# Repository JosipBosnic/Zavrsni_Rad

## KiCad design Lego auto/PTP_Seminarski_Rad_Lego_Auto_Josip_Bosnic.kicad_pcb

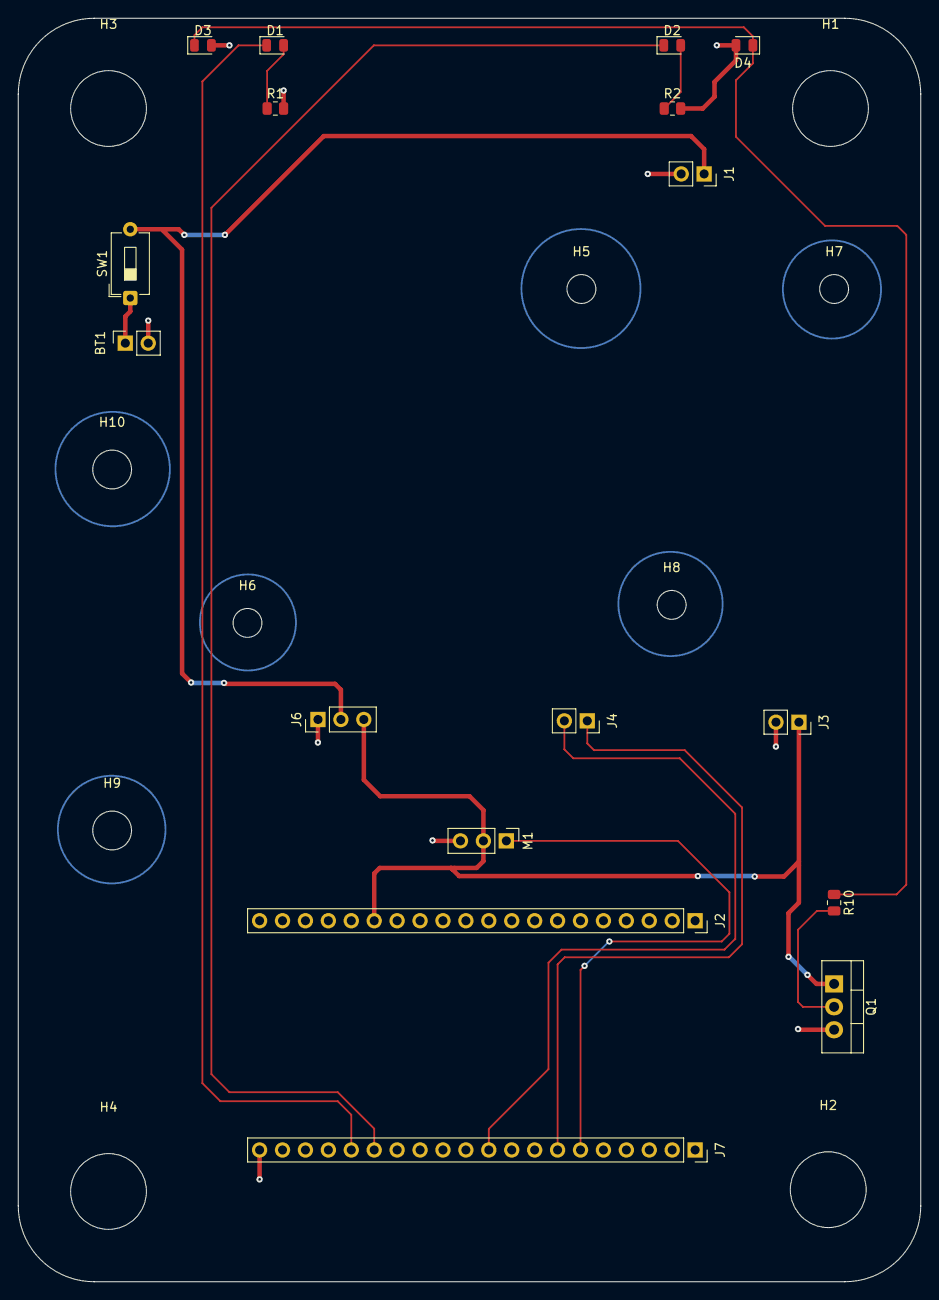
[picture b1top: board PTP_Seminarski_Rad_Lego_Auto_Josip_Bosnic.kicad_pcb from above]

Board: 2 copper layers, 100.0 x 140.0 mm, 27 parts (0 on the bottom side), 13 nets.

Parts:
BT1: Battery; PinSocket_1x02_P2.54mm_Vertical
D1, D2, D3, D4: LED; LED_0805_2012Metric
H1, H2, H3, H4: MountingHole; MountingHole_8.4mm_M8
H5: Hmost1; MountingHole_3.2mm_M3
H6: Hmost2; MountingHole_3.2mm_M3
H7: istosmjerni1; MountingHole_3.2mm_M3
H8: istosmjerni2; MountingHole_3.2mm_M3
H9: baterija1; MountingHole_4.3mm_M4
H10: baterija2; MountingHole_4.3mm_M4
J1, J3, J4: Conn_01x02; PinSocket_1x02_P2.54mm_Vertical
J2, J7: Conn_01x20_Socket; PinSocket_1x20_P2.54mm_Vertical
J6: Conn_01x03_Socket; PinHeader_1x03_P2.54mm_Vertical
M1: Motor_Servo; PinHeader_1x03_P2.54mm_Vertical
Q1: IRLZ44N; TO-220-3_Vertical
R1, R2, R10: 330 R; R_0805_2012Metric
SW1: SW_SPST; SW_DIP_SPSTx01_Slide_6.7x4.1mm_W7.62mm_P2.54mm_LowProfile

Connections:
+5V: J2.15, J3.1, J6.3, M1.2 (+), Q1.1 (G)
+BATT: J1.1, J6.2, SW1.2 (B)
-BATT: BT1.2 (-), D3.2 (A), D4.2 (A), J1.2, J3.2, J6.1, J7.20, M1.3 (-), Q1.3 (S), R1.2, R2.2
/IN1: J4.1, J7.7
/IN2: J4.2, J7.10
/servosignal: J7.6, M1.1 (PWM)
unnamed: BT1.1 (+), SW1.1 (A)
unnamed: D1.2 (A), R1.1
unnamed: D2.2 (A), R2.1
unnamed: Q1.2 (D), R10.2
Q1: D1.1 (K), J7.16
Q2: D2.1 (K), J7.15
Q3: D3.1 (K), D4.1 (K), R10.1

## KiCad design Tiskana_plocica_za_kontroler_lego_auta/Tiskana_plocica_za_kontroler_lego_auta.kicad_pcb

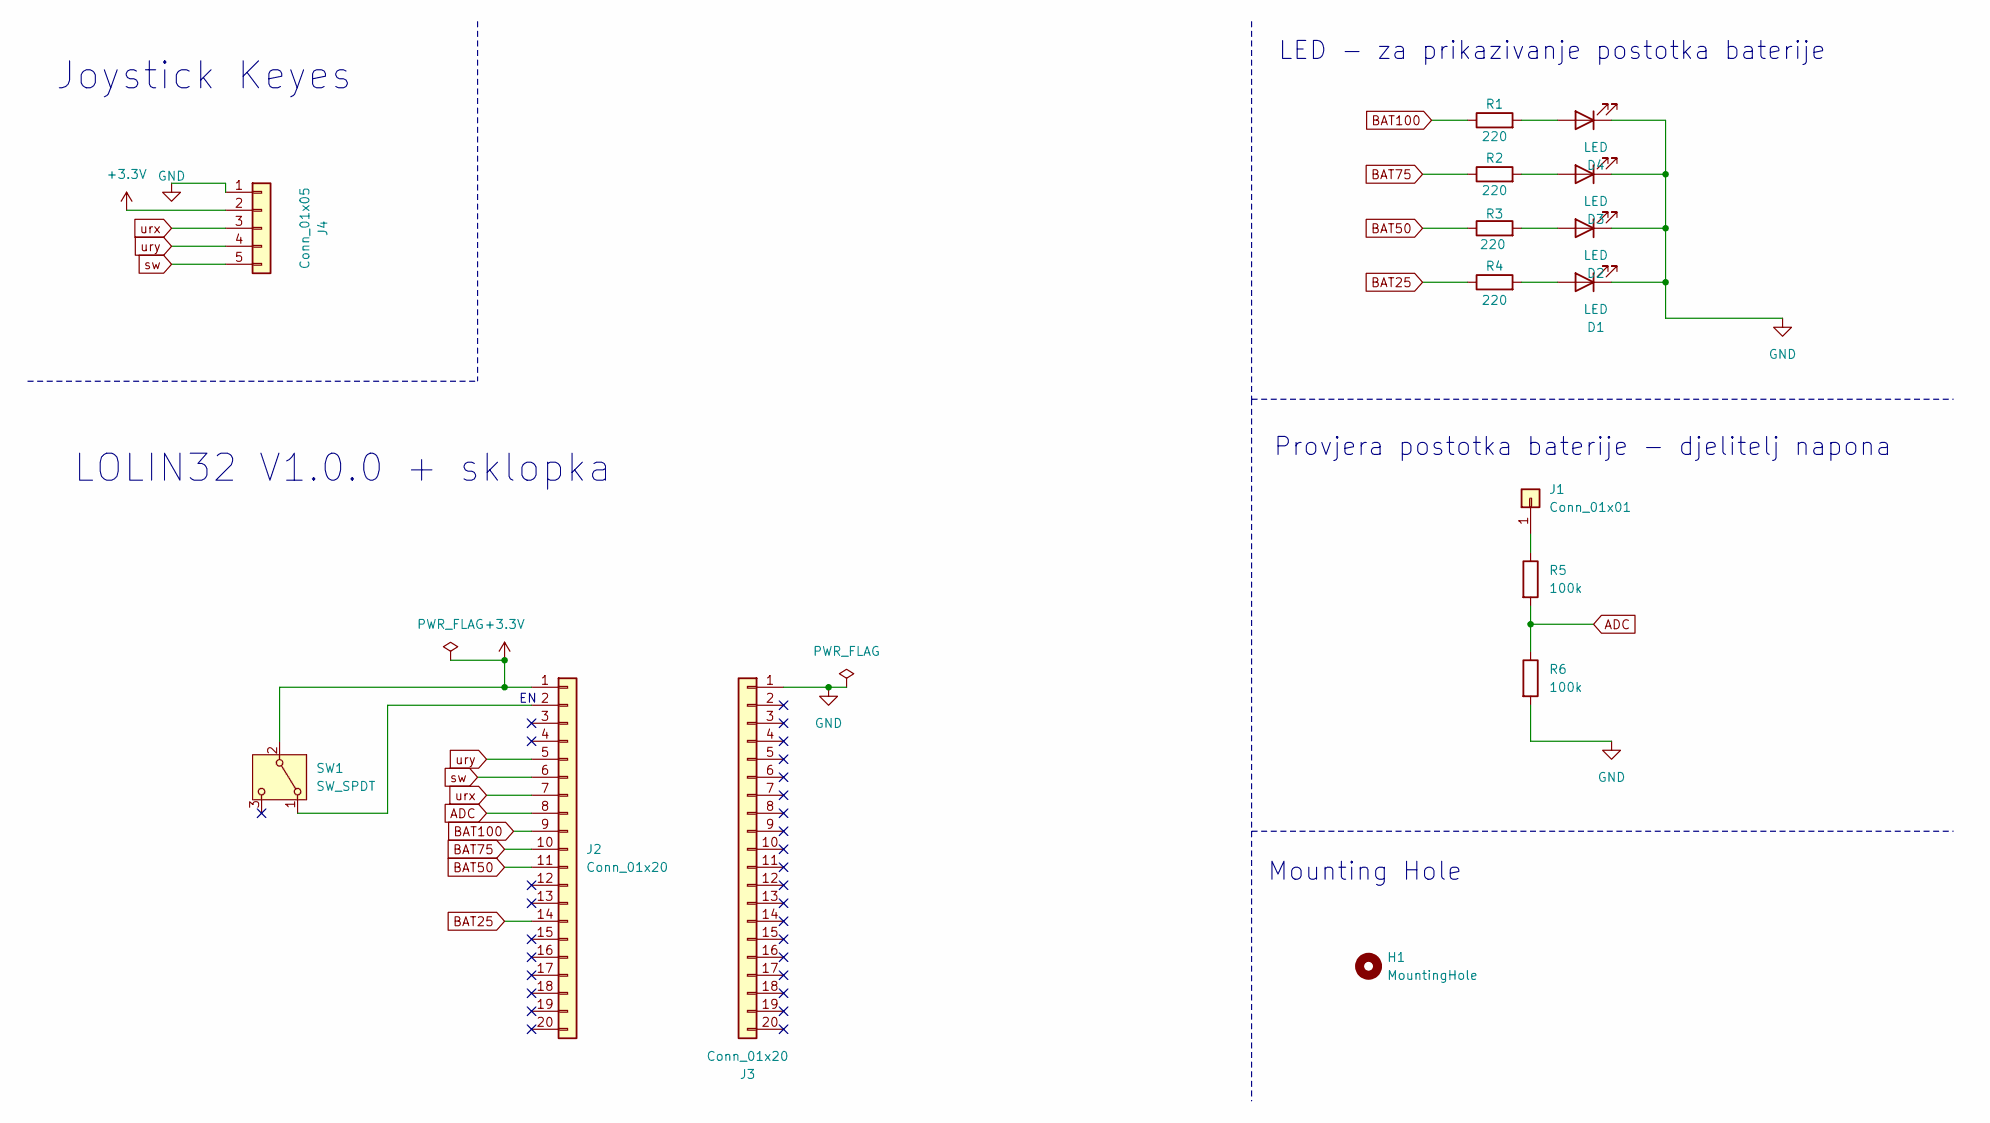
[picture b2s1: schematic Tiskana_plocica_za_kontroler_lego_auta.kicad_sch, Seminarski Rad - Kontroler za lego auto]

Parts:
D1, D2, D3, D4: LED; LED_0805_2012Metric
H1: MountingHole; MountingHole_5.3mm_M5
J1: Conn_01x01; PinSocket_1x01_P2.54mm_Vertical
J2, J3: Conn_01x20; PinSocket_1x20_P2.54mm_Vertical
J4: Conn_01x05; PinSocket_1x05_P2.54mm_Vertical
R1, R2, R3, R4: 220; R_0805_2012Metric
R5, R6: 100k; R_0805_2012Metric
SW1: SW_SPDT; SW_Slide-03_Wuerth-WS-SLTV_10x2.5x6.4_P2.54mm

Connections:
+3.3V: J2.1, J4.2, SW1.2 (B)
ADC: J2.8, R5.2, R6.1
BAT25: J2.14, R4.1
BAT50: J2.11, R3.1
BAT75: J2.10, R2.1
BAT100: J2.9, R1.1
GND: D1.1 (K), D2.1 (K), D3.1 (K), D4.1 (K), J3.1, J4.1, R6.2
unnamed: D1.2 (A), R4.2
unnamed: D2.2 (A), R3.2
unnamed: D3.2 (A), R2.2
unnamed: D4.2 (A), R1.2
unnamed: J1.1, R5.1
unnamed: J2.2, SW1.1 (A)
sw: J2.6, J4.5
urx: J2.7, J4.3
ury: J2.5, J4.4

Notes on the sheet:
Mounting Hole
LOLIN32 V1.0.0 + sklopka
Joystick Keyes
LED - za prikazivanje postotka baterije
Provjera postotka baterije - djelitelj napona

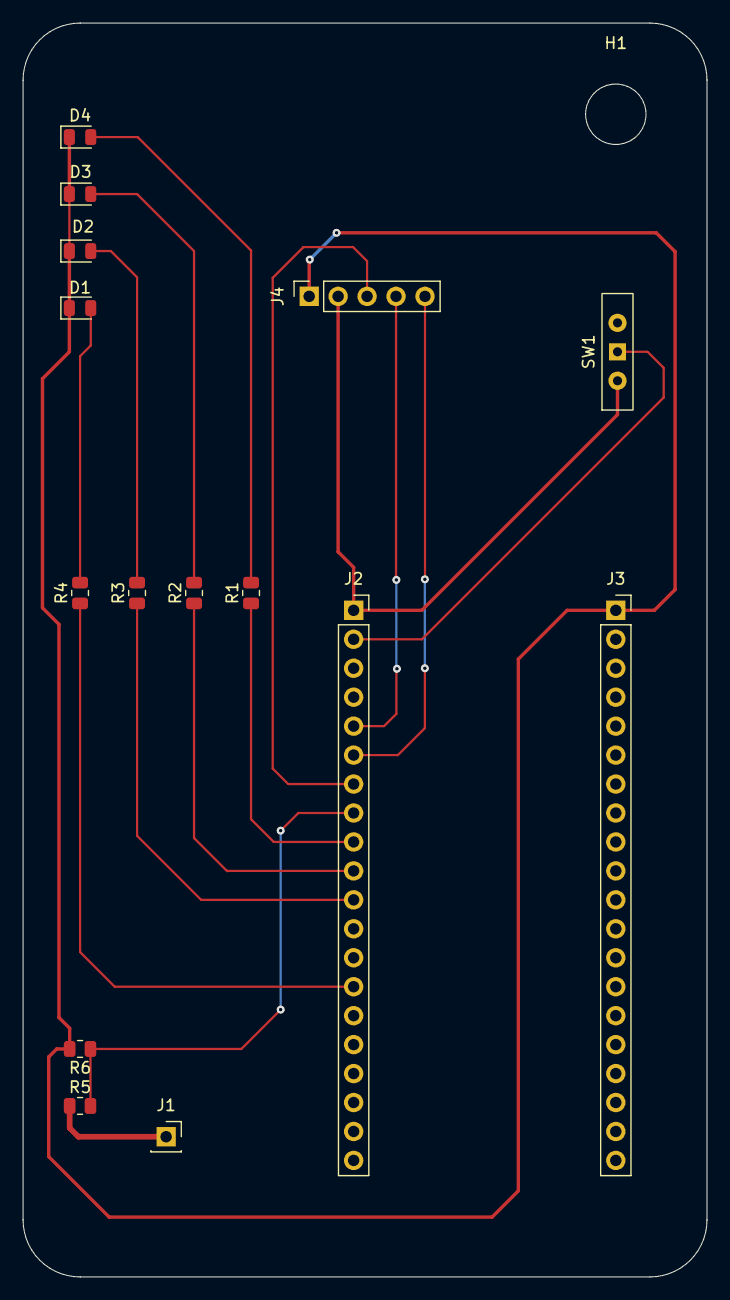
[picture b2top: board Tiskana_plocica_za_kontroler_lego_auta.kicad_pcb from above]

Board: 2 copper layers, 60.0 x 110.0 mm, 16 parts (0 on the bottom side), 16 nets.
